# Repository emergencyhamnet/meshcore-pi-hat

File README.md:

# MeshCore Raspberry Pi HAT

Non-commercial shared hardware design and manufacturing files for the custom Raspberry Pi HAT using the
Ebyte E22-900M33S radio module. Software is maintained separately in
[meshcore-pi-port](https://github.com/emergencyhamnet/meshcore-pi-port).

## Hardware v1.0

[Hardware v1.0 release record](RELEASE.md) describes the original fabrication package
and the later PCB source revision. The original package produced working boards with
hand-soldered fuses; the revised fuse-pad layout has not been fabrication-tested.
Read the known issues before ordering or assembling boards.

## Design Files

- [KiCad project](design/Lora_pi_Hat.kicad_pro), [schematic](design/Lora_pi_Hat.kicad_sch)
	and [PCB](design/Lora_pi_Hat.kicad_pcb). The PCB file reports KiCad generator version 10.0.
- [Schematic PDF](design/circuit.pdf).
- [Hardware specification, Issue 1.0](design/MeshCore_Pi_HAT_Hardware_Spec_Issue_1_0.rtf).
- [Updated assembly BOM](design/updated-Lora_pi_Hat.csv); not a complete procurement list.
- [Original fab-submitted package](fabrication/LORA-PI_HAT-V1.zip), preserved unchanged.

## Licence

Original project hardware design files, documentation and images use
[CC BY-NC-SA 4.0](https://creativecommons.org/licenses/by-nc-sa/4.0/): attribution,
non-commercial use and ShareAlike. This is non-commercial shared hardware, not
open-source hardware. [LICENSING.md](LICENSING.md) includes a separate permission to
pay a fabrication service for your own non-commercial builds. Commercial uses outside
those permissions require separate agreement. Third-party assets and software retain
their own licences.

## Software Compatibility

The Pi software's `v0.2.0-alpha5` release includes physical TXEN/RXEN GPIO control and
settings-save corrections for the tested E22 HAT. This does not certify all assemblies or
PCB revisions. Record the exact board and software revisions used for each hardware test.
The software TX-power setting represents requested SX1262 chip output, not final antenna
power; module-specific drive limits and RF compliance require verification.

## Electrical Safety

Disconnect all Pi, HAT and UPS power before fitting or removing the board. Verify supply
voltage, polarity, current capacity, GPIO logic levels and the fitted radio's specifications.
Use an appropriate antenna or RF load before transmitting. Analyzer connections require
suitable attenuation and power ratings. Observe applicable RF rules.

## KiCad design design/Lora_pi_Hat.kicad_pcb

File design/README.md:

# Editable Design Sources

Open `Lora_pi_Hat.kicad_pro` to work with the schematic and PCB. The PCB file reports
KiCad generator version 10.0; independent CAD opening, ERC/DRC and library completeness
have not been verified as part of this release.

The current PCB includes revised fuse pads that have not been fabricated. The original
working-board fabrication package is kept separately in `fabrication/`.
See [the release record](../RELEASE.md) before regenerating manufacturing outputs.

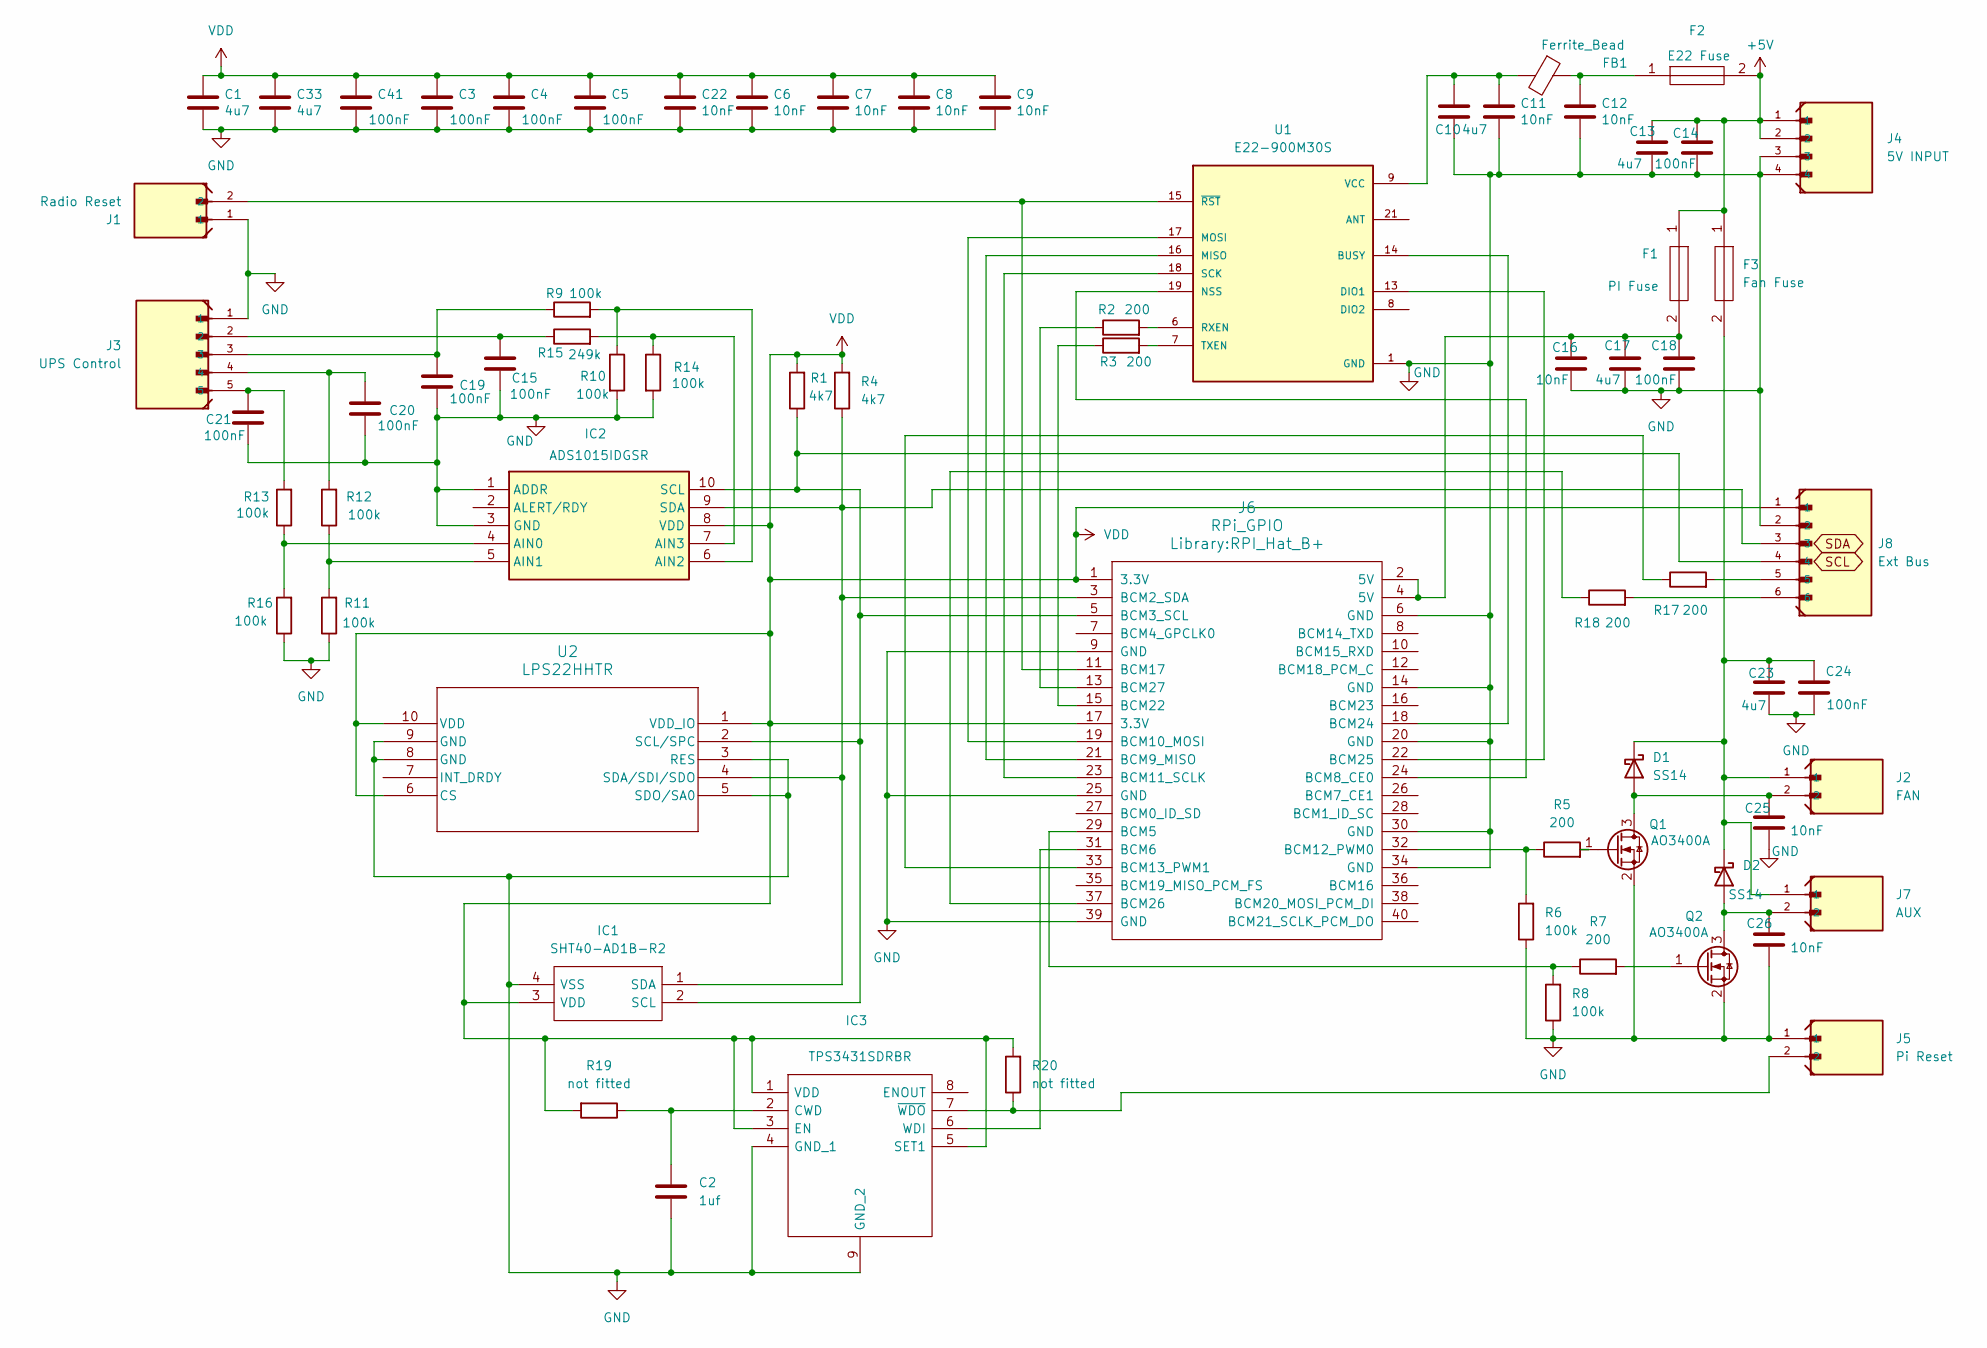
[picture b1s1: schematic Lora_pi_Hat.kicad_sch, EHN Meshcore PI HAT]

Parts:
C1, C10, C13, C17, C23, C33: 4u7; C_0805_2012Metric_Pad1.15x1.40mm_HandSolder
C2: 1uf; C_0603_1608Metric_Pad1.05x0.95mm_HandSolder
C3, C4, C5, C14, C15, C18, C19, C20, C21, C24, C41: 100nF; C_0603_1608Metric_Pad1.05x0.95mm_HandSolder
C6, C7, C8, C9, C11, C12, C16, C22, C25, C26: 10nF; C_0603_1608Metric_Pad1.05x0.95mm_HandSolder
D1, D2: SS14; D_SMA
F1: PI Fuse; FUSC4632X85N; Mouser Part Number 652-MF-MSMF200-2
F2: E22 Fuse; FUSC4632X85N; Mouser Part Number 652-MF-MSMF200-2
F3: Fan Fuse; FUSC4632X85N; Mouser Part Number 652-MF-MSMF200-2
FB1: Ferrite_Bead; 28F01811SR10
IC1: SHT40-AD1B-R2; SHT4X; Manufacturer_Part_Number SHT40-AD1B-R2; Mouser Part Number 403-SHT40-AD1B-R2
IC2: ADS1015IDGSR; DGS0010A_L; Mouser Part Number 595-ADS1015IDGSR
IC3: TPS3431SDRBR; SON65P300X300X100-9N-D; Mouser Part Number 595-TPS3431SDRBR
J1: Radio Reset; JST_B2B-PH-K-S_LF__SN_
J2: FAN; JST_B2B-PH-K-S_LF__SN_
J3: UPS Control; JST_B5B-PH-K-S
J4: 5V INPUT; JST_B4B-PH-K-S_LF__SN_
J5: Pi Reset; JST_B2B-PH-K-S_LF__SN_
J6: RPi_GPIO; RPI_Hat_B+
J7: AUX; JST_B2B-PH-K-S_LF__SN_
J8: Ext Bus; JST_B6B-PH-K-S
Q1, Q2: AO3400A; SOT-23
R1, R4: 4k7; R_0603_1608Metric_Pad0.98x0.95mm_HandSolder
R2, R3, R5, R7, R17, R18: 200; R_0603_1608Metric_Pad0.98x0.95mm_HandSolder
R6, R8, R9, R10, R11, R12, R13, R14, R16: 100k; R_0603_1608Metric_Pad0.98x0.95mm_HandSolder
R15: 249k; R_0603_1608Metric_Pad0.98x0.95mm_HandSolder
R19, R20: not fitted; R_0603_1608Metric_Pad0.98x0.95mm_HandSolder
U1: E22-900M30S; XCVR_E22-900M30S; PARTREV 1.2
U2: LPS22HHTR; HLGA-10L_2X2X0P73_STM

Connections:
+5V: C13.1, C14.1, F1.1, F2.2, F3.1, J4.1, J4.2
GND: C1.2, C2.2, C3.2, C4.2, C5.2, C6.2, C7.2, C8.2, C9.2, C10.2, C11.2, C12.2, C13.2, C14.2, C15.2, C16.2, C17.2, C18.2, C19.2, C20.2, C21.2, C22.2, C23.2, C24.2, C25.2, C26.2, C33.2, C41.2, IC1.4 (VSS), IC2.1 (ADDR), IC2.3 (GND), IC3.4 (GND_1), IC3.9 (GND_2), J1.1, J3.1, J4.3, J4.4, J5.1, J6.6 (GND), J6.9 (GND), J6.14 (GND), J6.20 (GND), J6.25 (GND), J6.30 (GND), J6.34 (GND), J6.39 (GND), J8.2, Q1.2 (S), Q2.2 (S), R6.1, R8.1, R10.2, R11.1, R14.2, R16.1, U1.1 (GND), U1.2 (GND), U1.3 (GND), U1.4 (GND), U1.5 (GND), U1.11 (GND), U1.12 (GND), U1.20 (GND), U1.22 (GND), U2.3 (RES), U2.5 (SDO/SA0), U2.8 (GND), U2.9 (GND)
unnamed: C12.1, F2.1, FB1.1
unnamed: C15.1, J3.2, R15.1
unnamed: C16.1, C17.1, C18.1, F1.2, J6.2 (5V), J6.4 (5V)
unnamed: C19.1, J3.3, R9.1
unnamed: C20.1, J3.4, R12.2
unnamed: C21.1, J3.5, R13.2
unnamed: C25.1, D1.2 (A), J2.2, Q1.3 (D)
unnamed: C23.1, C24.1, D1.1 (K), D2.1 (K), F3.2, J2.1, J7.1
unnamed: C26.1, D2.2 (A), J7.2, Q2.3 (D)
unnamed: IC1.2 (SCL), IC2.10 (SCL), J6.5 (BCM3_SCL), J8.4, R1.1, U2.2 (SCL/SPC)
unnamed: IC1.1 (SDA), IC2.9 (SDA), J6.3 (BCM2_SDA), J8.3, R4.1, U2.4 (SDA/SDI/SDO)
unnamed: IC2.4 (AIN0), R13.1, R16.2
unnamed: IC2.5 (AIN1), R11.2, R12.1
unnamed: IC2.6 (AIN2), R9.2, R10.1
unnamed: IC2.7 (AIN3), R14.1, R15.2
unnamed: C2.1, IC3.2 (CWD), R19.1
unnamed: IC3.6 (WDI), J6.31 (BCM6)
unnamed: IC3.7 (~WDO), J5.2, R20.1
unnamed: J6.29 (BCM5), R7.1, R8.2
unnamed: J6.24 (BCM8_CE0), U1.19 (NSS)
unnamed: J6.21 (BCM9_MISO), U1.16 (MISO)
unnamed: J6.19 (BCM10_MOSI), U1.17 (MOSI)
unnamed: J6.23 (BCM11_SCLK), U1.18 (SCK)
unnamed: J6.32 (BCM12_PWM0), R5.1, R6.2
unnamed: J6.33 (BCM13_PWM1), R17.1
unnamed: J1.2, J6.11 (BCM17), U1.15 (~RST)
unnamed: J6.15 (BCM22), R3.1
unnamed: J6.18 (BCM24), U1.14 (BUSY)
unnamed: J6.22 (BCM25), U1.13 (DIO1)
unnamed: J6.37 (BCM26), R18.1
unnamed: J6.13 (BCM27), R2.1
unnamed: J8.5, R17.2
unnamed: J8.6, R18.2
unnamed: Q1.1 (G), R5.2
unnamed: Q2.1 (G), R7.2
unnamed: R2.2, U1.6 (RXEN)
unnamed: R3.2, U1.7 (TXEN)
VCC: C10.1, C11.1, FB1.2, U1.9 (VCC), U1.10 (VCC)
VDD: C1.1, C3.1, C4.1, C5.1, C6.1, C7.1, C8.1, C9.1, C22.1, C33.1, C41.1, IC1.3 (VDD), IC2.8 (VDD), IC3.1 (VDD), IC3.3 (EN), IC3.5 (SET1), J6.1 (3.3V), J6.17 (3.3V), J8.1, R1.2, R4.2, R19.2, R20.2, U2.1 (VDD_IO), U2.6 (CS), U2.10 (VDD)

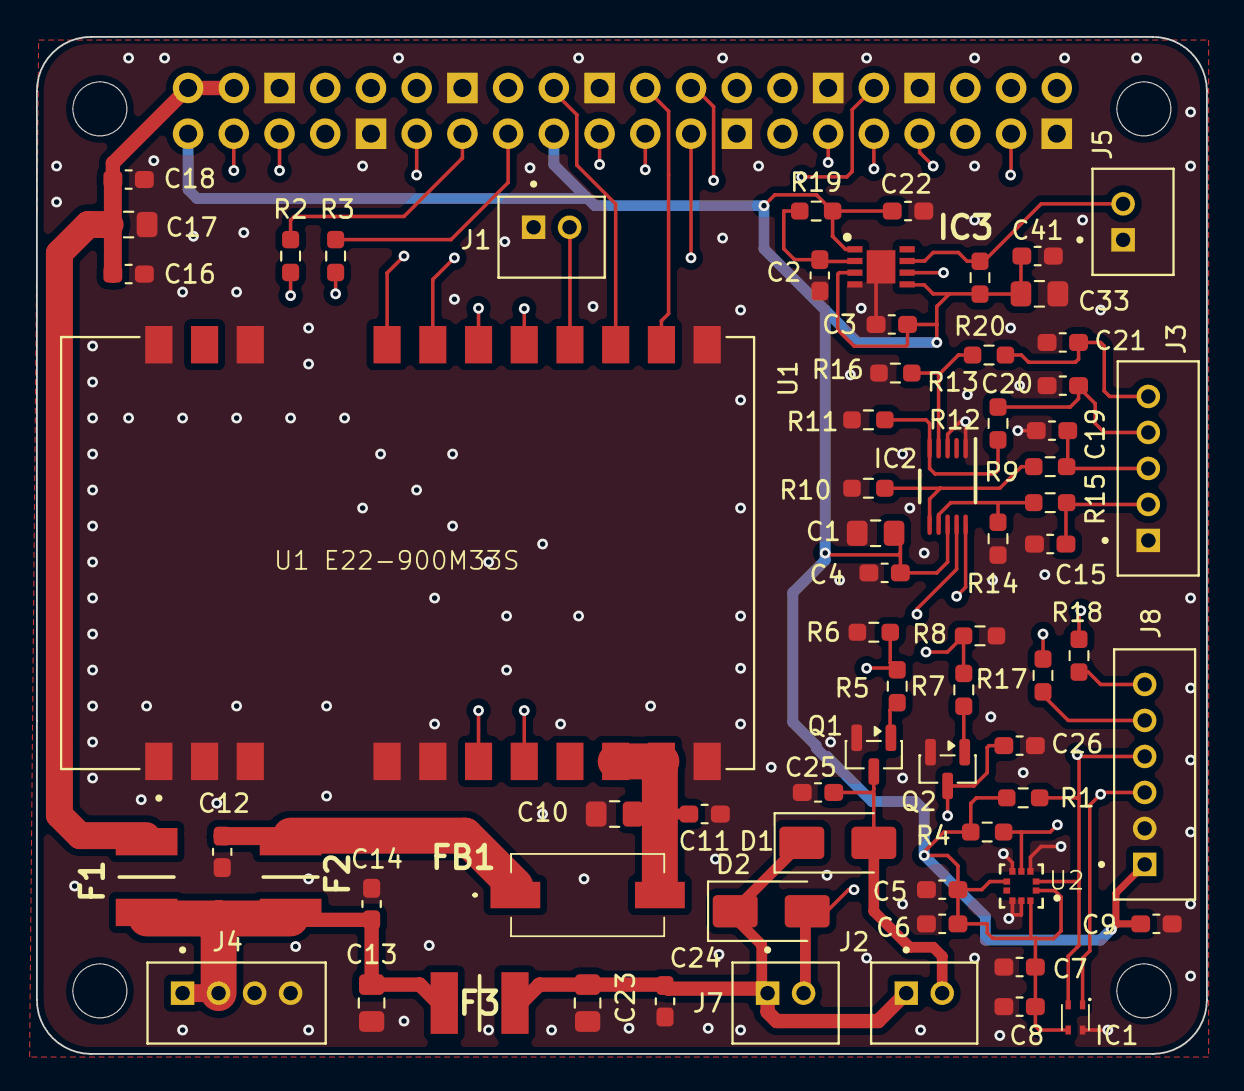
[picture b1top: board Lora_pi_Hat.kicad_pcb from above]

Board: 4 copper layers, 65.0 x 56.5 mm, 69 parts (0 on the bottom side), 41 nets.
